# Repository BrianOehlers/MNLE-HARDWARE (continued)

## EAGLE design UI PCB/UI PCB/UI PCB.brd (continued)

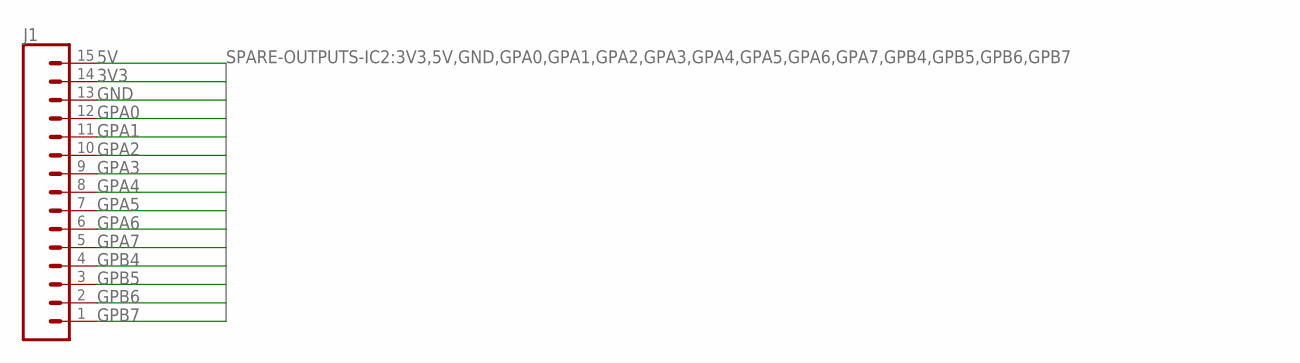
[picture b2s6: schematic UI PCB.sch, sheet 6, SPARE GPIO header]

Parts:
J1: CONN_15; 1X15

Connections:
3V3: J1.14; also elsewhere on the board
5V: J1.15; also elsewhere on the board
GND: J1.13; also elsewhere on the board
GPA0: J1.12; also elsewhere on the board
GPA1: J1.11; also elsewhere on the board
GPA2: J1.10; also elsewhere on the board
GPA3: J1.9; also elsewhere on the board
GPA4: J1.8; also elsewhere on the board
GPA5: J1.7; also elsewhere on the board
GPA6: J1.6; also elsewhere on the board
GPA7: J1.5; also elsewhere on the board
GPB4: J1.4; also elsewhere on the board
GPB5: J1.3; also elsewhere on the board
GPB6: J1.2; also elsewhere on the board
GPB7: J1.1; also elsewhere on the board

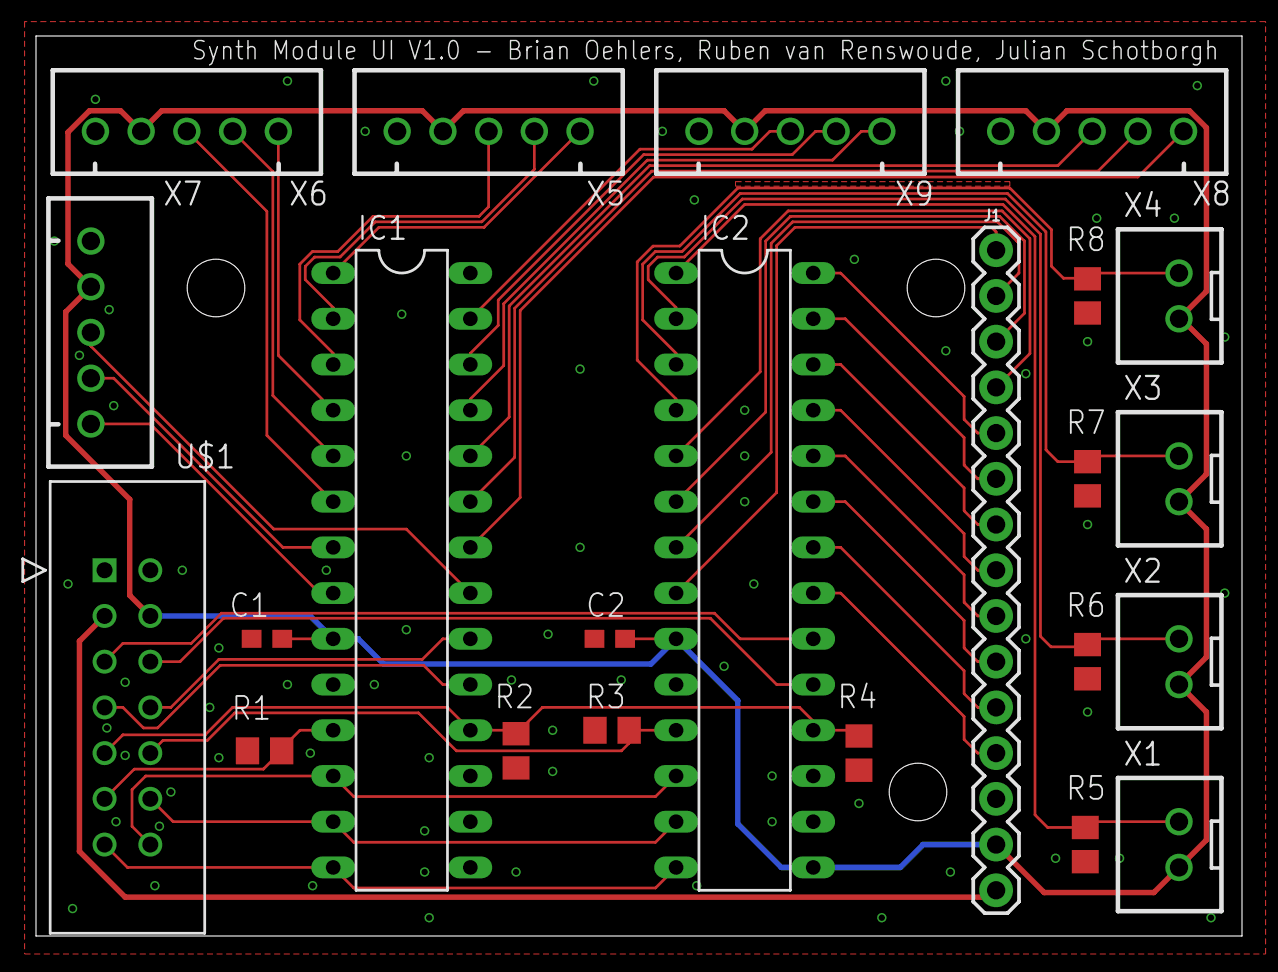
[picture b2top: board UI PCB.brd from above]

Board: 2 copper layers, 67.0 x 50.0 mm, 23 parts (0 on the bottom side), 44 nets.

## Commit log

2019-09-06 yeet
2019-09-06 branch del en map del
2019-10-17 Eagle schema opzet
2019-10-17 YM 4 chips in line edit
2019-11-12 M3 update 64 PIN
2019-11-12 M3 UPDATE LINES
2019-11-13 midi + optocoupler op blad 7. 3 nieuwe libraries.
2019-11-13 STM edit
2019-11-13 MIDI input andere weerstanden erin gedaan en wat layout aangepast. YM-klok aangemaakt, moet nog geriviewd worden.
2019-11-14 Review Ruben verwerkt: ontkoppel condensatoren voeding 6n136 en 7404.
2019-11-14 uploaden DIN5 lib.
2019-11-14 PINOUT M3 CHECK
2019-11-14 Sheet OUTPUTS
2019-11-14 changed footprints din connector and optocoupler
2019-11-14 OUTPUT final
2019-11-14 USB CONN
2019-11-14 Final merge
2019-11-14 BRD created
2019-11-14 FINAL VERSION - DAC NOG NIET GECONNECT
2019-11-14 DIG OUTPUT-PINNEN
2019-11-14 M4 - pin extended
2019-11-15 LCD BOOTLOADER HEADER
2019-11-18 Eerste versie PCB - Nog niet gerout/gerouted/geroutedt. Ter review voor plaatsing componenten.
2019-11-18 Eerste versie PCB
2019-11-19 Opamp wire change
2019-11-19 v2.0 - voldoet aan de DRC van JLPCB - PCB staat klaar voor review project groep.
2019-11-20 Added UI PCB design
2019-11-20 added descriptions for busses and sheets
2019-11-20 added libraries and a part of the PCB design
2019-11-20 v2.5 - IO expander update - moet nog steeds gepeerreviewd worden.
2019-11-20 improve the schemetic on the io expanders and add the right header for the stm32 connection
2019-11-21 v3.0 - PCB review aangepast
2019-11-21 redesigned PCB
2019-11-21 put every trace on top layer
2019-11-21 revieuw met ruben mondelijk gedaan, wat aangepast - nieuwe versie is dit.
2019-11-21 V4.0 ON/OFF Button/LED
2019-11-21 Schroefgaten toegevoegd
2019-11-21 review door Ruben met een paar changes
2019-11-21 Toevoegen namen op pcb
2019-11-21 PCB V5.0 LDO Adjustment
2019-11-21 V5.1 Connectors edit
2019-11-25 some changes to PCB design, thicker power supply lines
2019-11-26 Nieuwe versie - aanpassing aan: componenten, ground, namen van componenten, usb verschoven
2019-11-26 component namen geresized en verplaatst.
2019-11-26 verandere jumpers en verplaatsen din en usb.
2019-11-26 update lcd header
2019-11-26 gerber files
2019-11-26 gerber files toegevoegd
2019-11-26 nieuwe gerber files toegevoegd
2019-11-26 uiteindelijke gerber files met holes goed uitgelijnd
2019-11-26 Randen en holes op mm grid
